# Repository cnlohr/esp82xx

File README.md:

# esp82xx

Useful ESP8266/ESP8285 C Environment.
Includes libraries and some basic functionality such as a Web-GUI, flashing firmware and changing the UI over network as well as basic GPIO functions.

You can use it as a template for your own ESP8266/ESP8285 projects.
Just include it as sub-module in derivate projects.

NOTE: If you are starting from another environment or from the factory, you should execute ```make erase initdefault``` this will set the flash up in a way compatible with the newer ESP NONOS SDK 2.x's.

**Contributors,** please read the notes closely before you start (e.g. [Branches](#branches) and [Include Binaries](#include-binaries)).
Make changes in the `dev` branch!

- [List of projects using esp82xx](#list-of-projects-using-esp82xx)
- [Usage](#usage)
    - [Requirements](#requirements)
    - [Start a new Project](#start-a-new-project)
    - [Specify SDK](#specify-sdk)
    - [Burn Firmware](#burn-firmware)
    - [Connect to your Module](#connect-to-your-module)
    - [Commands](#commands)
    - [Troubleshooting](#troubleshooting)
- [Notes](#notes)
    - [Create File Structure by hand](#create-file-structure)
    - [Branches](#branches)
    - [Submodule Updates](#submodule-updates)
    - [Include Binaries](#include-binaries)
- [ToDo](#todo)

## List of projects using esp82xx

 - [esp82XX-basic](https://github.com/con-f-use/esp82XX-basic) (or the one in cnlohr's account (should be up to date) [esp82XX-basic cnlohr](https://github.com/con-f-use/esp82XX-cnlohr)
 - [Colorchord](https://github.com/cnlohr/colorchord)
 - [MAGFest Swag](https://youtu.be/DbjlStyMmaY?t=8m) [Badges 2017](https://github.com/cnlohr/swadges2017)
 - [esp8266ws2812i2s](https://github.com/cnlohr/esp8266ws2812i2s)
 - [espusb](https://github.com/cnlohr/espusb)
 - [channel3 NTSC Broadcasting](https://github.com/cnlohr/channel3/)
 - [Minecraft on an ESP8266 via avrcraft](https://github.com/cnlohr/avrcraft)
 - Migration of others in progress

## Usage / Install

### Requirements

*Most of this is written having a Debian-like Linux distribution in mind.
You will need to use your imagination, if you want to build on other platforms.
People have done it on OSX and Win 7/8.
Look at open and closed issues and internet resources on the SDK such as the
 [esp-forum](http://www.esp8266.com/search.php?search_id=active_topic) to find help.*

You will need the following:

 - [Espressif](https://espressif.com) toolchain for the esp82xx-series chips
 - [Libusb](http://libusb.info) 1.0 (`sudo apt-get install libusb-1.0-0-dev`)
 - GNUMake
 - GNU Compiler Collection and build essentials
 - Possible more

### Install the Prerequisites and SDK.

#### Prerequisites (Windows (WSL))
 * Install WSL 1 using these instructions: https://docs.microsoft.com/en-us/windows/wsl/install-win10
 * Reboot.
 * Install Ubuntu 20.04: https://www.microsoft.com/en-us/p/ubuntu-2004-lts/9n6svws3rx71?rtc=1
 * Launch Ubuntu 20.04
 * Install Python 2 and make separately
 ```
 sudo apt update
 sudo apt install python make
 ```
 * Proceed with normal prerequisites and project.

#### Prerequisites (Debian, Mint, Ubuntu):
```
sudo apt-get update
sudo apt-get install -y make gcc g++ gperf install-info gawk libexpat-dev python2-dev python2 python2-serial sed git unzip bash wget bzip2 libtool-bin
```

Note: Some platforms do not have python-serial, or any version of Python 2 for that matter (since it has reached its end of life on Jan 1, 2020 and all tooling and hosting is dropping support for it). If they don't have pip, but do still have python 2, do this:
```
curl  https://github.com/pypa/get-pip/raw/5f38681f7f5872e4032860b54e9cc11cf0374932/get-pip.py --output get-pip.py
sudo python2 get-pip.py
pip install pyserial
```
Otherwise, you have to use a distribution that has Python 2 packaged, compile it and the missing dependencies yourself, from source, or wait until the tools used here are ported to Python 3.

#### Install
This will install the SDK to ~/esp8266 - the default location for the ESP8266 SDK.  This only works on 64-bit x86 systems, and has only been verified in Linux Mint and Ubuntu.  Installation is about 18MB and requires about 90 MB of disk space.

```
mkdir -p ~/esp8266
cd ~/esp8266
wget https://github.com/cnlohr/esp82xx_bin_toolchain/raw/master/esp-open-sdk-x86_64-20200810.tar.xz
tar xJvf esp-open-sdk-x86_64-20200810.tar.xz
```

Several esp82xx projects use the offical Espressif nonos SDK instead of the bundled one here.  You should probably install that to your home folder using the following commands:

```
cd ~/esp8266
git clone https://github.com/espressif/ESP8266_NONOS_SDK --recurse-submodules
```

Optional: Add your user to the dialout group:
```
sudo usermod -aG dialout cnlohr
```

Caveat: On Windows Subsystem for Linux, you will need to find your serial port.  You will need to alter `PORT=` in user.cfg in the tool you are building.

See Appendix A and B for alternate options (if you are on non-64-bit x86 systems)

Some versions of the SDK are somewhat problematic, e.g. with SDK versions greater than 1.5.2, Espressif changed the IRAM management, so some projects began to hit size restrictions and would not compile.
Also some SDKs use different initial data (the flash has to have some SDK-related settings stored that are not userspace and aren't flashed along with the firmware).
For that reason, the Makefile is set up to use a [customized version](https://github.com/cnlohr/esp_nonos_sdk) of the SDK and ships with proven initial data.

#### Specify SDK

If your SDK is not installed to `~/esp8266/esp-open-sdk`, then there are many ways to [let Make know where your SDK is](https://github.com/cnlohr/esp82xx/issues/19#issuecomment-241756095) located.
You can edit `DEFAULT_SDK` in `./user.cfg` to reflect your specific SDK path or **even better** define a shell variable.
The latter is done with

    # Add this in ~/.bashrc or similar
    export ESP_ROOT=/path/to/sdk/where/esp-open-sdk

in your `.bashrc`, `.profile` or whatever is used by your shell. This way, the change will be persistent, even if you start many new esp82xx projects.

You can also pass the location as an argument to make:

    make all ESP_ROOT=/path/to/sdk/where/esp-open-sdk

### Start a new Project

Starting a new project based on esp82xx is pretty easy:

    mkdir my_new_esp_project
    cd my_new_esp_project
    git clone --recursive https://github.com/cnlohr/esp82xx
    cp esp82xx/Makefile.example Makefile
    make project

Replace the last line by the line below, if you also want to initialize the folder as a new git repo and upload it to a remote location:

    make gitproject GIT_ORIGIN=https://github.com/YOUR_USER/YOUR_NEW_REPO.git

Alternatively, you can add esp82xx as a submodule from your project as follows:

    git add submodule https://github.com/cnlohr/esp82xx
    cp esp82xx/Makefile.example Makefile
    make project

After the above commands, provided you have [specified the SDK](#specify-sdk), the basic file structure should be in place.
Most files will be symbolic links against files in `./esp82xx/`.
**Do not** edit these files or anything in `./esp82xx/`.
You should rather copy the files to the top-level directories and edit the copies where necessary.
I.e. if you want add a line of CSS that changes the font in the WebUI, copy `./esp82xx/web/page/intex.html` to `./web/page/` overwriting the symbolic link.
Then make your edits.

Edit `user.cfg` in the top level to specify things like the location of the Espressif toolchain (see [Requirements](#requirements)).
The file  `user.cfg` specifies the most important configuration variables.

### Burn Firmware

If you did everything correctly, flashing your esp should work.
Just connect it to an USB to serial adapter that uses 3.3V (**you will fry your ESP with voltages higher than 3.3 V**) and place it in programming mode.

For the first run from a factory or unknown source of an ESP, you should run the following command to completely wipe it and give it new data:

```
    make burnitall
```

Then you can run

```
    make burn
    make burnweb  # programming mode here too
```

and your ESP is good to go.
It should create its own WiFi Access Point called `ESPXXXX` or similar, where `XXXX` is some arbitrary code.
From now on you can configure and burn new firmware/page data over the web interface in your browser (when connected to the esp's network or it is connected to yours).
There are make targets to burn firmware and page data as well:

    make netburn IP=192.168.4.1  # default IP, change to whatever your ESP is set to
    make netweb IP=192.168.4.1

To find out the IP, see below.

### Connect to your Module

The ESP will print its connection info, including its current IP to the serial interface after reset/power-on.

You can [connect to the ESP](http://esp82xx.local) in your browser:

    http://esp82xx.local

There is also a make-target called `getips` that scans for ESP modules and lists their IPs.
`make getips` is basically a port-scan, that uses external tools you might have to install and takes long (especially if no ESP is connected).

The default IP of the ESP, when it operates as it's own access point, is **192.168.4.1**.
When connected to an existing WiFi Network, it will ask your DHCP-Server for an IP.
Most WiFi routers have an option in their Web-GUI to list all IPs, that their DHCP has given out.
You could find out your ESP's IP this way.

For general troubleshooting hints, see [esptools troubleshooting page](https://github.com/themadinventor/esptool#troubleshooting).
It is excellent!

### Commands

Most features of the WebUI can be used over network by sending an ASCII string to the flashed ESP.
This way you can evoke a feature from a program, script or the shell (i.e. using `nc` a.k.a netcat).

The command string starts with a letter signifying the command or family of commands.
In case of a command family, the second letter usually defines the command.
After that comes the first argument.
Subsequent arguments after the first are usually followed by tab-characters.
Most commands will also send a response packet containing information or error codes.
The character(s) that specify the command(-family) are not case sensitive, i.e. `E1234` and `e1234` will be interpreted identically.

Here is an example to get a freshly flashed ESP to connect to a WiFi network named `MyWiFi`:
```
echo -ne "W1\tMyWiFi\t1234\ta1:b2:c3:d4:e5:f6\t1" | nc 192.168.4.1 7878  -u -w 1 | hexdump -C

```
The access point has the mac `a1:b2:c3:d4:e5:f6` and password `1234`.
The program `hexdump` is used to receive and display the ESP's answer.

The commands are:

| Family | Command | Description |
| :----: | :-----: | ----------- |
| **B**  |         | **Browse commands** |
|        | q       | Probe |
|        | s       | Service name |
|        | l       | List IP, service, device name and description |
|        | r       | Response |
|        |         |  |
| **G**  |         | **GPIO commands** |
|        | 0       | Turn pin with the same number as the first argument on |
|        | 1       | Turn pin with the same number as the first argument off |
|        | i       | Make pin numbered same as the first argument an input |
|        | f       | Toggle pin number specified by the first argument |
|        | g       | Get status of pin numbered same as the first argument |
|        | s       | Get outputmask and rmask as base-ten numbers |
|        |         |  |
| **E**  | .       | **Echo command string with all arguments (for test purposes)** |
|        |         |  |
| **I**  |         | **Get info** |
|        | b       | Restart system |
|        | s       | Save CS-settings |
|        | l       | Load CS-settings 1 |
|        | r       | Load CS-settings 2 |
|        | f       | Start finding devices or return list of found devices |
|        | n       | Device name |
|        | d       | Device description |
|        | .       | General info: IP, device name, description, servie name, free heap |
|        |         |  |
| **W**  |         | **Wifi commands** |
|        | 0       | Have the ESP an AP. Arguments: AP name, password, mac, channel |
|        | 1       | Connect to existing network AP. Same arguments as above |
|        | i       | Get info on current Wifi settings |
|        | x       | Get RSSI (if applicable) and current IP |
|        | s       | Scan for WiFi stations |
|        | r       | Return results of scan |
|        |         |  |
| **F**  |         | **Flashing commands** |
|        | e       | Erase sector |
|        | b       | Erase block |
|        | m       | Execute flash rewriter |
|        | w       | Write given number of bytes to flash (binary) |
|        | x       | Write given number (second argument) of hexadecimal bytes (third argument) to position in (first argument) in flash |
|        | r       | Read a number of bytes (second argument) from a sector (first argument) flash |
| **C**  |         | ** Custom commands ** |
|        | C       | Respond with 'CC' |
|        | E       | Echo arguments to UART |
|        | ...     | Your commands could go here |
|        |         |  |

A dot `.` stands for an omitted character, i.e. nothing.
It is not included in the command string.

For more information on these commands, please conuslt the source code.
The commands are implemented in `./esp82xx/fwsrc/commonservices.c`.
You can add your own commands in `./user/custom_commands.c`.

## Troubleshooting

### Caught in Reset loop

Most of endless resets are caused by one of the following:
 - Power supply too weak (the esp can draw 300mA)
 - Not enough decoupling capacitance (a combination of 100uF and  100nF work)
 - Wonky connection (worn out, loose or dirty contacts
 - Initial flash data faulty (see [Specify SDK](#specify-sdk)), in which case this might help:
 ```
 make erase
 make initdefault #init3v3
 ```

### Gibberish Serial Data right after Boot

If you get weird data at the start of your serial communication with the esp, don't forsake!
The boot ROM writes a log to the UART with the unusual timing of 74880 baud.
It's normal.

### Useful Links

 - [esp8266 Getting Started Guide](https://espressif.com/en/support/explore/get-started/esp8266/getting-started-guide)
 - [esp-forum](http://www.esp8266.com/search.php?search_id=active_topic)
 - [NodeMCU docs](https://nodemcu.readthedocs.io/en/master/en/flash/)

## Notes

This section should mostly concern developers and contributors to this project.
We try to keep the generally interesting stuff on top.

### Create File Structure

You can create the file structure of a basic program by hand or based on another project, instead of running `make project`.
To do that first, check out a project that uses esp82xx

    git clone --recursive https://github.com/con-f-use/esp82XX-basic

or create your own

    git init project_name
    cd project_name
    git submodule add https://github.com/cnlohr/esp82xx.git
    cp esp82xx/user.cfg.example user.cfg
    cp esp82xx/Makefile.example Makefile
    cp esp82xx/fwsrc/user . -a
    mkdir -p web/page user
    ln -s ../esp82xx/web/Makefile web/
    # ... link or copy more files depending on how much you want to change ...

After that, you can push it a freshly created remote repository with the usual git commands:

    git init .
    git add .
    git git remote add origin https://github.com/YOUR_USER/YOUR_NEW_REPO.git
    git commit -m 'Initial commit'
    git push

The basic Makefile for the firmware is `./esp82xx/main.mf`.
Most things can be achieved by including it in your top-level Makefile and changing some make variables.

    include esp82xx/main.mf

    SRCS += more_sources.c # Add your project specific sources

### Branches

If you make small incremental changes and/or experimental ones, push to the `dev` branch rather than to origin/master:

    git push origin dev

You can merge or squash-merge them into `master` once they have been tested and enough changes accumulate.

    # ... Make changes in dev ...
    # ... test them and be sure they should go into master ...
    git checkout master
    git merge --squash dev
    git commit

It might be good to create feature branches to develop individual features and merge them into `dev`.

### Submodule Updates

Cope with submodule changes in top-level project:

 - You made changes in the submodule and want to push them:

    ```
    cd esp82xx   # is the submodules here
    # Make changes in esp82xx
    git commit -m 'Your Message'
    git push     # pushes to the sumodule remote
    ```
    Make sure you're in the 'dev' branch.
    You can check that with `git branch`.
    If you're not, make sure to `git checkout dev` first, BEFORE you make your changes.
    You can also use `git push origin dev` to push just the dev branch.

    When you're ready to push, first make sure 'master' is up to date with
    `git push origin dev:master`.
    Then to push to master, use `git push origin dev:master`

 - Bump esp82xx version in the main project root folder:

    ```
    cd esp82xx
    git pull
    cd ..
    git add esp82xx
    git commit -m 'Bumped submodule version'
    git push
    ```

 - Make sure you are using the master branch of your submodules, when you're about to merge a dev version of top-level projects.
 I.e. just before you merge, checkout the master branch of submodules, so that when you merge, a Master-branch top-level projects uses the master-branch of all its submodules and not subodule dev-braches.

 - You can clone the dev-branch directly:

    ```
    git clone --recursive -b dev https://github.com/cnlohr/esp82xx.git && cd esp82xx
    ```

   If you forgot and switched to `dev` via `git checkout dev`, you might not have the proper submodules. In that case run `git submodule update --init`

### Include Binaries

You should **not** include binaries in the project repository itself.
There is a make target that builds the binaries and creates a `.zip` file. Included that in the release.
To make a release, just tag a commit with `git tag -a 'v1.3.3.7' -m 'Your release caption'` and push the tag with `git push --tags`.

After that, the github web-interface will allow you to make a release out of the new tag and include the binary file.
To make the zip file invoke `make projectname-version-binaries.tgz` (Tab-autocompletion is your friend).

## ToDo

 - Include libraries for usb, ws2812s and ethernet
 - Expand the "Requirements" section

# Troubleshooting

If you see something like this:

```
rf_cal[0] !=0x05,is 0xE9

 ets Jan  8 2013,rst cause:2, boot mode:(3,6)

load 0x40100000, len 25936, room 16 
tail 0
chksum 0x20
load 0x3ffe8000, len 1272, room 8 
tail 0
chksum 0x9b
load 0x3ffe8500, len 1212, room 8 
tail 4
chksum 0x8c
csum 0x8c
```
You may not be loading your parititon tables properly.  #1 check user.cfg to make sure you have your partition burning location set correctly. 

Additionally, make sure you are loading the partition tables in your user_main.

```
void user_pre_init(void)
{
	//You must load the partition table so the NONOS SDK can find stuff.
	LoadDefaultPartitionMap();
}
```

# Appendices

## Appendix A: Installing the pfalcon SDK

We recommend the excellent [esp-open-sdk](https://github.com/pfalcon/esp-open-sdk) by @pfalcon.
It downloads and installs the Espressif toolchain.
Here is a shell script to [download and build](https://gist.github.com/con-f-use/d086ca941c2c80fbde6d8996b8a50761) a version known to work.
You should read and understand the script, before running it.
It will take some time and GBs of disk space to build the toolchain.

## Appendix B: Alternate (Manual) pfalcon SDK Linux Setup

Prerequisites (Debian, Mint, Ubuntu):
```
sudo apt-get update
sudo apt-get install -y make unrar autoconf automake libtool gcc g++ gperf flex bison texinfo-doc-nonfree install-info info texinfo gawk ncurses-dev libexpat-dev python-dev python python-serial sed git unzip bash help2man wget bzip2 libtool-bin
```

esptool:

```
cd ~/esp8366
git clone --recursive https://github.com/igrr/esptool-ck.git || exit 1
cd esptool-ck
make
cd ..
```

pfalcon's SDK:

```
cd ~/esp8266

git clone --recursive https://github.com/pfalcon/esp-open-sdk.git
cd esp-open-sdk

# For legacy projects, you will need SDK 1.5.2, from before espressif filled the iram
#sed -i 's/^\(\s*VENDOR_SDK\s*=\s*\).*$/\1 1.5.2/' Makefile
#git checkout e32ff685 # Old version of sdk (v1.5.2) before espressif filled the iram

make STANDALONE=y 
find . -name "c_types.h" -exec cp "{}" "{}.patched" \;

# Line below fixes a bug, when e32ff685 or other old versions are used
#find -type f -name 'c_types.h.orig' -print0 | while read -d $'\0' f; do cp "$f" "${f%.orig}"; done
```

You may want to manually add the SDK path to your bashrc.  Copy out the note from makefile and
paste it into your .bashrc.

```
nano ~/.bashrc
```

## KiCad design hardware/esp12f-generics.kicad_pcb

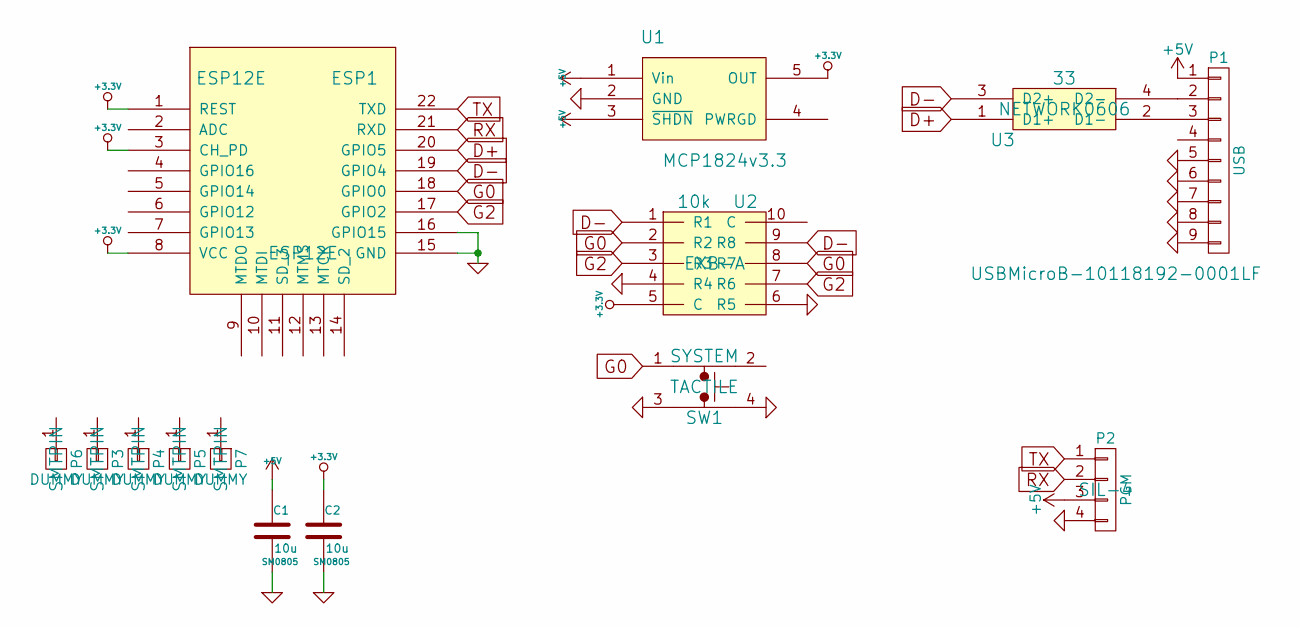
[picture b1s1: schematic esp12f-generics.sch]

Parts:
C1, C2: 10u; SM0805; Digikey 1276-6456-1-ND
ESP1: ESP12E
P1: USB; USBMicroB-10118192-0001LF; Digikey 609-4613-1-ND
P2: PGM; SIL-4
P3, P4, P5, P6, P7: DUMMY; SMTPIN
SW1: SYSTEM; TACTILE; Digikey EG4621CT-ND
U1: MCP1824v3.3; SOT-23-5; Digikey MCP1824T-3302E/OTCT-ND
U2: 10k; EXB-A; Digikey U7103CT-ND
U3: 33; NETWORK0606; Digikey 742C043330JPCT-ND

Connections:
+3.3V: C2.1, ESP1.1 (REST), ESP1.3 (CH_PD), ESP1.8 (VCC), U1.5 (OUT), U2.5 (C)
+5V: C1.1, P1.1, P2.3, U1.1 (Vin), U1.3 (~SHDN)
D+: ESP1.20 (GPIO5), U3.1 (D1+)
D-: ESP1.19 (GPIO4), U2.1 (R1), U2.9 (R8), U3.3 (D2+)
G0: ESP1.18 (GPIO0), SW1.1, U2.2 (R2), U2.8 (R7)
G2: ESP1.17 (GPIO2), U2.3 (R3), U2.7 (R6)
GND: C1.2, C2.2, ESP1.15 (GND), ESP1.16 (GPIO15), P1.5, P1.6, P1.7, P1.8, P1.9, P2.4, SW1.3, SW1.4, U1.2 (GND), U2.4 (R4), U2.6 (R5)
unnamed: P1.2, U3.4 (D2-)
unnamed: P1.3, U3.2 (D1-)
RX: ESP1.21 (RXD), P2.2
TX: ESP1.22 (TXD), P2.1

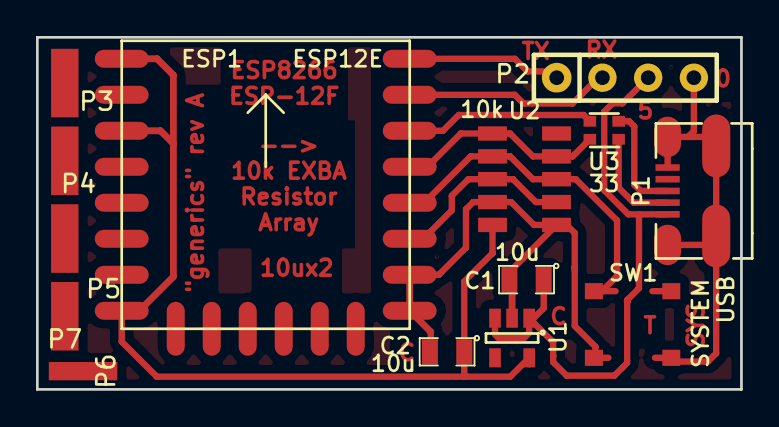
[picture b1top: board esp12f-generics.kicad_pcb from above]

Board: 2 copper layers, 39.1 x 19.6 mm, 14 parts (0 on the bottom side), 11 nets.

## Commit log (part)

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2016-08-18 Add an initial file
    Initial readme, before pull from con-f-use's work
2016-08-18 Useful ESP8266 C Environment
2016-08-18 Add missing jquery file
2016-08-19 Various makefile robustness and cleanup changes.
2016-08-19 Fix web page to load image locally and allow conditionals on some of the common files.
2016-08-19 * Add warnings about usb burning * Fix Makefile so 'make clean' doesn't delete your .S files!
2016-08-19 update main.cf to add note about all, and add debugging symbols compile step
2016-08-19 Closes #6 - switched to grayscale and used pngcrush. 349 bytes raw. Much smaller encdoed into webpage.
2016-08-19 Get esp82xx automatically with Makefile.example
2016-08-19 Fix code formatting in README
2016-08-19 Extend list of projects
2016-08-19 Add a makefile flag for bumping submodules
2016-08-19 Auto-pull submodule without a rule
2016-08-20 Update with parameterized selection for where the webpage goes.
2016-08-21 No need to claim, only release kernel.
2016-08-21 Generalize user config, disable docker support by default
2016-08-21 Add -e in order to make it OSX-compatible.
2016-08-22 More useful info in README
2016-08-22 Notes for developes in README and formatting
2016-08-22 Add CLEAN_EXTRA variable to specify extra clean targets in the top-level make files (optional)
2016-08-22 Verify flash when DEBUG enabled
2016-08-22 Fix readme
2016-08-22 Refs #5 - add the suggested command. Probably should figure something out WRT non-existant parameters.
2016-08-23 Closes #18 - Now flash loader only takes 205 bytes and change.
2016-08-23 Tighten down the use of FLASH
2016-08-23 Preprocessor constants for Timeout and Maxtries
2016-08-23 Improve readme
2016-08-23 Add Table of Contents in README
2016-08-24 Closes #17! This also cuts down on the total stuff in IRAM, still not enough to fit most projects into the 2.x SDKs. :-(
2016-08-24 Override variables with inside_docker and outside_docker funtions instead of littering with . Thanks @con-f-use for the tips
2016-08-24 Added some documentation on experimental docker support, correct typos.
2016-08-24 Fix README typos
    Thanks to @brainstrom for catching this!
2016-08-24 Fix character swap in README
    Thanks to @brainstorm for catching this
2016-08-24 Hint at Troubleshooting in README
2016-08-24 Netburn should be executed outside docker too
2016-08-24 Clarified docker usage a bit
2016-08-25 Revert "Support for Docker and OSX for esp-open-sdk toolchain"
2016-08-27 Added -fm dio into make burn for 8266 because ESP-12E modules on some (not all) NodeMCU boards, are dual I/O and will only work with --flash_mode dio.
2016-08-27 add notice about which chip is being burned.
2016-08-27 Add missing include (that keeps on getting lost)
2016-08-29 Change `echo` to Make built-in
2016-09-03 Add dumprom, fix #32.
2016-09-04 add hardware example for an ESP-12-F board mounted to a single-layer PCB.
2016-09-04 Seems to fix #35.
2016-09-04 Fixed #35 by solving #33
2016-09-05 Update to facilitate additional packet control, for manually overridden libraries.
2016-09-06 Allow custom linker scripts also notify when done flashing. Sometimes they don't reboot. Why?
2016-09-06 Page PAGE_SCRIPT more useful
2016-09-06 Backwards compatability?
2016-09-06 Big cleanup of reboot, makefiles and web page
    Squashed commit of the following:
    commit 1cf23008f9ab0d3d96fc27428d9c4201002d68a7
    Author: con-f-use <con-f-use@gmx.net>
    Date: Tue Sep 6 19:16:49 2016 +0200
    Modularize javascript using poor man templating
    commit abfe173b011643ab1b0c7c7716657c0a886aa283
2016-09-06 Forgot to clean web Makefile
2016-09-07 Small bugfix for script inclusion
2016-09-24 Add MIME types for gzipped js and css
2016-09-24 Add date -R switch to unlocalize build time
2016-09-24 Add gzip MIME types and delocalize build date (#39)
    * Big cleanup of reboot, makefiles and web page
    Squashed commit of the following:
    commit 1cf23008f9ab0d3d96fc27428d9c4201002d68a7
    Author: con-f-use <con-f-use@gmx.net>
    Date: Tue Sep 6 19:16:49 2016 +0200
    Modularize javascript using poor man templating
2016-10-03 Add better control for custom dynamic webpages.
2016-10-08 Make esp82xx play better with a non-sdk environment.
2017-01-01 Expose connection status.
2017-01-15 Fix for SDK 1.5.4
2017-01-29 add to src files
2017-01-30 fix build for newer SDK to put program at right place.
2017-01-30 Fix up MANY lose ends!
2017-01-30 further tweaking
2017-01-30 Move liblwip to flash
2017-02-04 Update with better note about linker script
2017-02-06 Start a new project via `make project`
2017-02-16 Add missing 'user_rf_cal_sector_set()'
2017-02-18 Update user_main.c
    Use recommended setup for cal flash map.
2017-03-02 Add 'make gitproject' and reflect changes in readme
    Needs to be tested!
    Also added the sdk as a submodule. Still need to change paths in the makefiles and test it.
    DO NOT USE THIS COMMIT
2017-03-03 Do not require Bash shell
2017-03-03 Small cleanups
2017-03-03 Add recursive pulling to README
2017-04-06 readme: typos
2017-04-06 version generator use date +rfc3339 format because date -R is not supported on OSX
2017-05-12 Document commands in `./commonsercies.c`
2017-05-12 Fix typo in README.md
2017-05-13 Minor hotfixes (strcat, ESP_DEFAULT, README.md)
2017-05-16 Level dev and master (#55)
    * Start a new project via `make project`
    * Fix minor error cleaning rules
    * Add missing 'user_rf_cal_sector_set()'
    * Update user_main.c
    Use recommended setup for cal flash map.
    * Add sdk, 'make gitproject', inprove 'make project'
2017-05-17 Closes #13 - Add support by switching protocol to binary and providing most users in Javascript space the same string, though the binary blob is also now available.
2017-05-17 USe esp82xx version if top-level not a git project
2017-05-20 Typo fix
2017-05-20 Minor typos in README.md - Thanks to @bbkiwi
2017-05-20 Typo in README.md regarding default IP (missed one)
2017-05-20 Fixed typo of typo fix :-)
2017-05-23 Put the strup function in flash.
2017-06-19 Properly write flash (fix issue #61)
2017-06-19 Fix not saving wifi credentials when flash size not 512K
    Changed hardcoded contant to real flash size determined by SDK at firmware start.
2017-06-19 Fix OTA upgrade bug and repair saving WiFi credentials
    1. removed skipping one byte from firmware sent by web
    2. size of flash chip now not hardcoded, will be restored correctly, so system parameters will be saved for all flash sizes, not only for 512K
2017-06-25 Fetch toolchain automatically if missing
2017-07-16 Changes needed to make esp82xx interact properly with colorchord Added EnterCritical() and ExitCritical() to ensure that ADC is not running when it will interfer with connection to station, and other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
2017-07-22 Fix bug that -DQUIET_REFLASH didn't work
2017-07-25 Fix various WiFi and net-flashing issues
    Squashed commit of the following:
    commit 7bbbfa36049ef543b37c0426ae7afdabae9fa206
    Merge: 5f72094 7a9ddd6
    Author: con-f-use <con-f-use@users.noreply.github.com>
    Date: Sat Jul 22 07:59:06 2017 +0200
    Merge pull request #69 from bbkiwi/devpull
2017-08-19 Add CUSTOM_FAIL_BEHAVIOR, and make significant performance improvements in the netburning features.
2017-09-02 Disable GPIO0 resetting.
2017-09-13 Closes #72 - add esp_reset tool.
2018-01-13 Fix for new SDK
2018-06-06 Add "burnitiall"
2018-06-06 add note for burn it all
2018-06-07 Update - allow disabling of auto AP switch.
2018-06-07 It is not worth the pain of showing passwords.
2018-10-16 Remove first birnitall target
    This fixes a warning when building
2018-10-16 Readded burnitall target for 8285
2018-10-21 Updated .gitmodules
2018-10-22 Got it compiling with nonos-3.0
2018-10-24 Fixed settings address & makefile for nonos-3.0 SDK
2018-10-24 Added makefile help
2018-10-24 Updated MFS location
    Updated burnitall targets
2018-10-26 Added ESP-NOW lib, moved MFS again
2018-10-27 Added prototype for strcat
2018-10-29 Removed submodule
2018-10-29 Switched to my submodule with new libs
2018-10-29 Coppied in UART code from SDK 3.0
2018-11-08 Switched to os_printf, ets_* functions
2018-11-10 Added new submodule
2018-11-10 Removed submodule, take 2
2018-11-10 Updated submodule?
2018-11-10 Removed submodule, take 3
2018-11-15 Updated user_main.c with partition registering, comments.
    Added back charrx() functions to uart.c. These were lost when pulling in
    the 3.0 UART code
2018-11-16 Removed ICACHE_FLASH_ATTR from EnterCritical() and ExitCritical()
2018-11-16 Updated user.cfg.example
2018-11-16 Update only needed changes so far... will need to reorganize partition map, but that will be later.
2018-11-17 Reverted the changes from b2656dc3e6e822b3d375548cbd77f112b3cb8ccd and 2c11783ae646375ba7db3366503fe476eac2ef91
    This revision should be equivalent to 719ca28a7c5e6efc94308869707debb4f8e75b14
2018-11-18 allow for building of a stripped libgcc
2018-11-18 Significant improvements for netflashing and minor improvements for IRAM
2018-11-18 add note about disabled NET_REFLASH
2018-11-18 Fix bug when trying to scan for networks.
2018-11-18 move partition table information to esp82xx so the burnden isn't on slave projects.
2018-11-18 Switch mechanism for symbol stripping
2018-11-20 esp82xx now uses SOFTAP_CHANNEL instead of a hardcoded 1
2018-11-21 functionify the GPIO functionality
2019-03-13 Update esp_nonos_sdk submodule
2019-03-24 Fix all warnings
    Added __attribute__((unused)) on unused params
    Explicitly cast between signed and unsigned variables
    Preprocess out or remove unused variables
    Clean up loop logic (gcc warns about assignments happening in logic)
    Move or add function declarations
    Replace calls to SHA1_Init() with calls to SHA1Init(), etc
2019-03-24 Bump submodule
2019-03-28 Removed strcat, it is provided elsewhere
2019-03-28 fix warnings
2019-04-24 updated submodule
2019-06-30 Fix -Wshadow warnings
2019-06-30 Fix -Wstrict-prototypes warnings
2019-06-30 Fixed -Wswitch-default warnings
2019-07-08 adjustment to flash firmware/page.mpfs via webgui
2020-01-03 Allow init data location to be different, for instance when flashing the MAGFest Swadges.
2020-08-09 Add example system nonos sdk.
2020-08-09 Remove incorrect notes about system nonos sdk.
2020-08-09 Make esp82xx able to use new or old SDKs
2020-08-11 * Fix IO issue on newer compilers. * Add notes for super simple SDK install. * Add correct warning for MPFS location
2020-08-11 fix typeo for burnitall
2020-08-11 update note about proper init rom location
2020-08-12 Don't use MAKE to substitute the path for esptool.
2020-08-12 Fix dependencies for burnitall.
2020-08-26 Or continue to use python 2?
    Other way: 'apt purge python3' so it don't get conflicted when installing pyserial
2020-08-26 fix typo
2020-08-27 Actually it is python, not python2
2020-08-30 Install make and python separately on WSL
    WSL somehow does not want to install python and make when installing with other program
2021-01-31 readme: python 2 EoL
2021-10-28 ignore libgcc_strippped.a
2021-10-30 ignore libgcc_stripped.a - happens if building with STRIPPED_LIBGCC
2021-10-30 Makefile: improve release/zip targets - allow overriding PROJECT_NAME (useful if doing CI builds / docker and the mounted directory name is generic) - new target 'zip_release' (more human-friendly al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
